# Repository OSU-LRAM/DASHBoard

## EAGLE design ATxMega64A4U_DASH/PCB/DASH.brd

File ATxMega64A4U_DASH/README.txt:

Bluetooth Device ID:
RNBT-990E

Authentification is:
1234

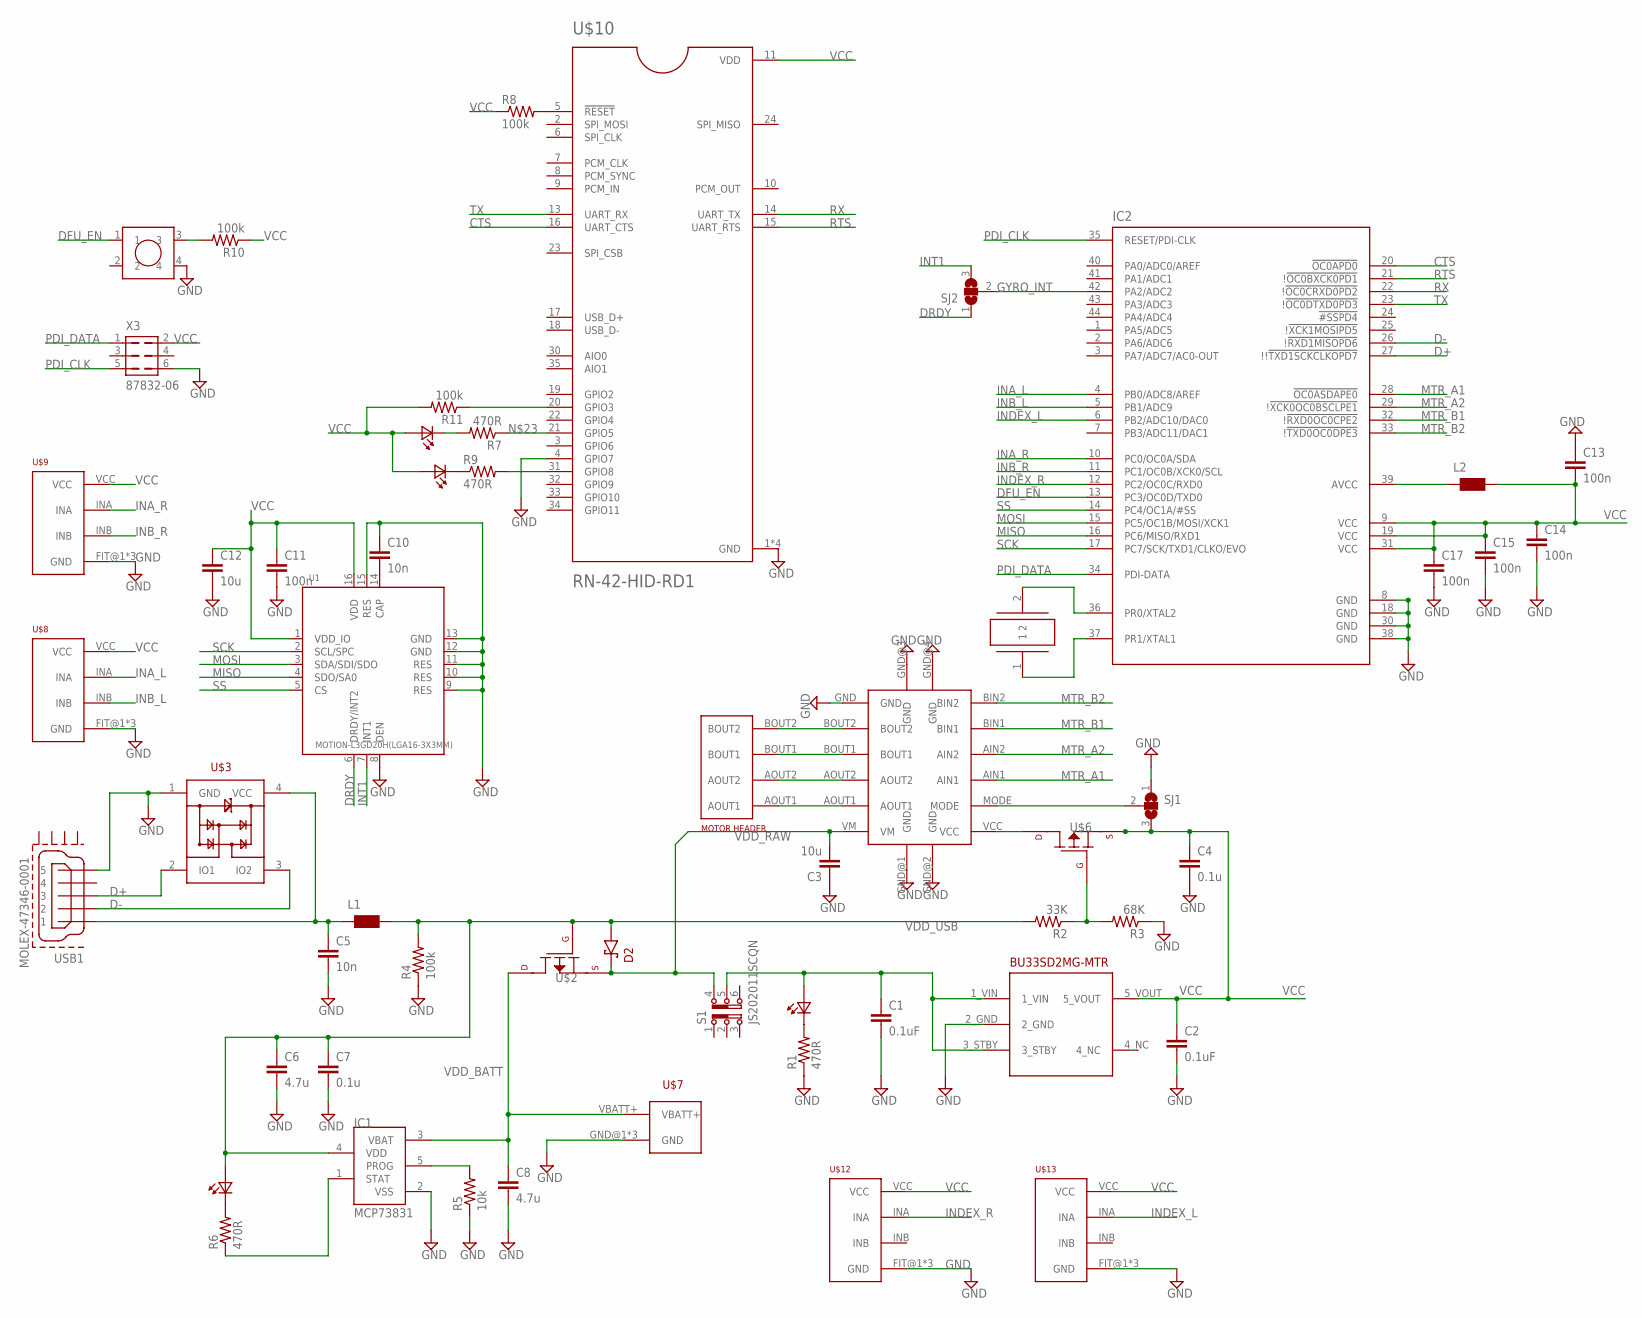
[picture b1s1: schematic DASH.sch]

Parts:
C1, C2: 0.1uF; 0603-CAP
C3, C12: 10u; C0805
C4, C7: 0.1u; C0603
C5, C10: 10n; C0603
C6, C8: 4.7u; C0603
C11, C13, C14, C15, C17: 100n; C0603
D1, D3, D5, D6: LTST-C190KRKT; 0603
D2: SCHOTTKY_DIODE_0805
IC1: MCP73831; SOT23-5L
IC2: AT-XMEGA-XXA4-AU; QFP80P1200X1200X120-44N
L1, L2: WE-CBF_0603; 0603
R1, R6, R7, R9: 470R; R0603
R2: 33K; R0603
R3: 68K; R0603
R4, R8, R10, R11: 100k; R0603
R5: 10k; R0603
S1: JS202011SCQN
SJ1, SJ2: SJ2W; SJ_2
U1: MOTION-L3GD20H(LGA16-3X3MM); LGA16-0.5-3X3MM
U$1: LDO_BU33SD2-MSURFACE_MOUNT; SSOP5
U$2, U$6: P-FETSMD; SOT-323
U$3: PRTR5V0U2X; SOT143B
U$4: DRV8835
U$5: SMB04-SRSS-TBSMD; SM04B-SRSS-TB
U$7: SM02B-SRSS
U$8, U$9, U$12, U$13: LEFT_ENCODER; SM04B-SRSS-TB
U$10: RN-42-HID-RD1; MICROCHIP_RN-42-HID-RD1
U$11: PUSHBUTTON
U$14: FC-12M_32.7
USB1: MOLEX-47346-0001; MOLEX-47364-0001
X3: 87832-06

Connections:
CTS: IC2.20 (!OC0APD0), U$10.16 (UART_CTS)
D+: IC2.27 (!!!TXD1SCKCLKOPD7), U$3.2 (IO1), USB1.3
D-: IC2.26 (!!RXD1MISOPD6), U$3.3 (IO2), USB1.2
DFU_EN: IC2.13 (PC3/OC0D/TXD0), U$11.1
DRDY: SJ2.1, U1.6 (DRDY/INT2)
GND: C1.2, C2.2, C3.1, C4.2, C5.2, C6.2, C7.2, C8.2, C10.1, C11.2, C12.2, C13.1, C14.2, C15.2, C17.2, IC1.2 (VSS), IC2.8 (GND), IC2.18 (GND), IC2.30 (GND), IC2.38 (GND), R1.1, R3.1, R4.1, R5.1, SJ1.1, U1.8 (DEN), U1.9 (RES), U1.10 (RES), U1.11 (RES), U1.12 (GND), U1.13 (GND), U1.15 (RES), U$1.2_GND, U$3.1 (GND), U$4.GND, U$4.GND@1 (GND), U$4.GND@2 (GND), U$4.GND@3 (GND), U$4.GND@4 (GND), U$4.GND@5 (GND), U$7.GND@1 (GND), U$7.GND@2 (GND), U$7.VBATT- (GND), U$8.FIT@1 (GND), U$8.FIT@2 (GND), U$8.GND, U$9.FIT@1 (GND), U$9.FIT@2 (GND), U$9.GND, U$10.1 (GND), U$10.4 (GPIO7), U$10.12 (GND), U$10.28 (GND), U$10.29 (GND), U$11.4, U$12.FIT@1 (GND), U$12.FIT@2 (GND), U$12.GND, U$13.FIT@1 (GND), U$13.FIT@2 (GND), U$13.GND, USB1.5, X3.6
GYRO_INT: IC2.42 (PA2/ADC2), SJ2.2
INA_L: IC2.4 (PB0/ADC8/AREF), U$8.INA
INA_R: IC2.10 (PC0/OC0A/SDA), U$9.INA
INB_L: IC2.5 (PB1/ADC9), U$8.INB
INB_R: IC2.11 (PC1/OC0B/XCK0/SCL), U$9.INB
INDEX_L: IC2.6 (PB2/ADC10/DAC0), U$13.INA
INDEX_R: IC2.12 (PC2/OC0C/RXD0), U$12.INA
INT1: SJ2.3, U1.7 (INT1)
MISO: IC2.16 (PC6/MISO/RXD1), U1.4 (SDO/SA0)
MOSI: IC2.15 (PC5/OC1B/MOSI/XCK1), U1.3 (SDA/SDI/SDO)
MTR_A1: IC2.28 (!OC0ASDAPE0), U$4.AIN1
MTR_A2: IC2.29 (!!XCK0OC0BSCLPE1), U$4.AIN2
MTR_B1: IC2.32 (!!RXD0OC0CPE2), U$4.BIN1
MTR_B2: IC2.33 (!!TXD0OC0DPE3), U$4.BIN2
unnamed: C1.1, D1.2 (A2), S1.5, U$1.1_VIN, U$1.3_STBY
unnamed: D1.1 (K2), R1.2
unnamed: R10.2, U$11.3
unnamed: U$4.AOUT1, U$5.AOUT1
unnamed: C10.2, U1.14 (CAP)
unnamed: U$4.AOUT2, U$5.AOUT2
unnamed: U$4.BOUT1, U$5.BOUT1
unnamed: U$4.BOUT2, U$5.BOUT2
unnamed: U$4.VCC, U$6.3_DRAIN
unnamed: R2.1, R3.2, U$6.1_GATE
unnamed: SJ1.2, U$4.MODE
unnamed: C5.1, L1.1, U$3.4 (VCC), USB1.1
unnamed: D3.1 (K2), R6.2
unnamed: IC1.5 (PROG), R5.2
unnamed: IC1.1 (STAT), R6.1
unnamed: D5.1 (K2), R7.2
unnamed: D6.1 (K2), R9.1
unnamed: IC2.36 (PR0/XTAL2), U$14.2
unnamed: IC2.37 (PR1/XTAL1), U$14.1
unnamed: IC2.39 (AVCC), L2.1
unnamed: R9.2, U$10.31 (GPIO8)
unnamed: R8.2, U$10.5 (!RESET)
unnamed: R7.1, U$10.21 (GPIO5)
unnamed: R11.1, U$10.20 (GPIO3)
PDI_CLK: IC2.35 (RESET/PDI-CLK), X3.5
PDI_DATA: IC2.34 (PDI-DATA), X3.1
RTS: IC2.21 (!!OC0BXCK0PD1), U$10.15 (UART_RTS)
RX: IC2.22 (!!OC0CRXD0PD2), U$10.14 (UART_TX)
SCK: IC2.17 (PC7/SCK/TXD1/CLKO/EVO), U1.2 (SCL/SPC)
SS: IC2.14 (PC4/OC1A/#SS), U1.5 (CS)
TX: IC2.23 (!!OC0DTXD0PD3), U$10.13 (UART_RX)
VCC: C2.1, C4.1, C11.1, C12.1, C13.2, C14.1, C15.1, C17.1, D5.2 (A2), D6.2 (A2), IC2.9 (VCC), IC2.19 (VCC), IC2.31 (VCC), L2.2, R8.1, R10.1, R11.2, SJ1.3, U1.1 (VDD_IO), U1.16 (VDD), U$1.5_VOUT, U$6.2_SOURCE, U$8.VCC, U$9.VCC, U$10.11 (VDD), U$12.VCC, U$13.VCC, X3.2
VDD_BATT: C8.1, IC1.3 (VBAT), U$2.3_DRAIN, U$7.VBATT+
VDD_RAW: C3.2, D2.1_CATHODE, S1.4, U$2.2_SOURCE, U$4.VM
VDD_USB: C6.1, C7.1, D2.2_ANODE, D3.2 (A2), IC1.4 (VDD), L1.2, R2.2, R4.2, U$2.1_GATE

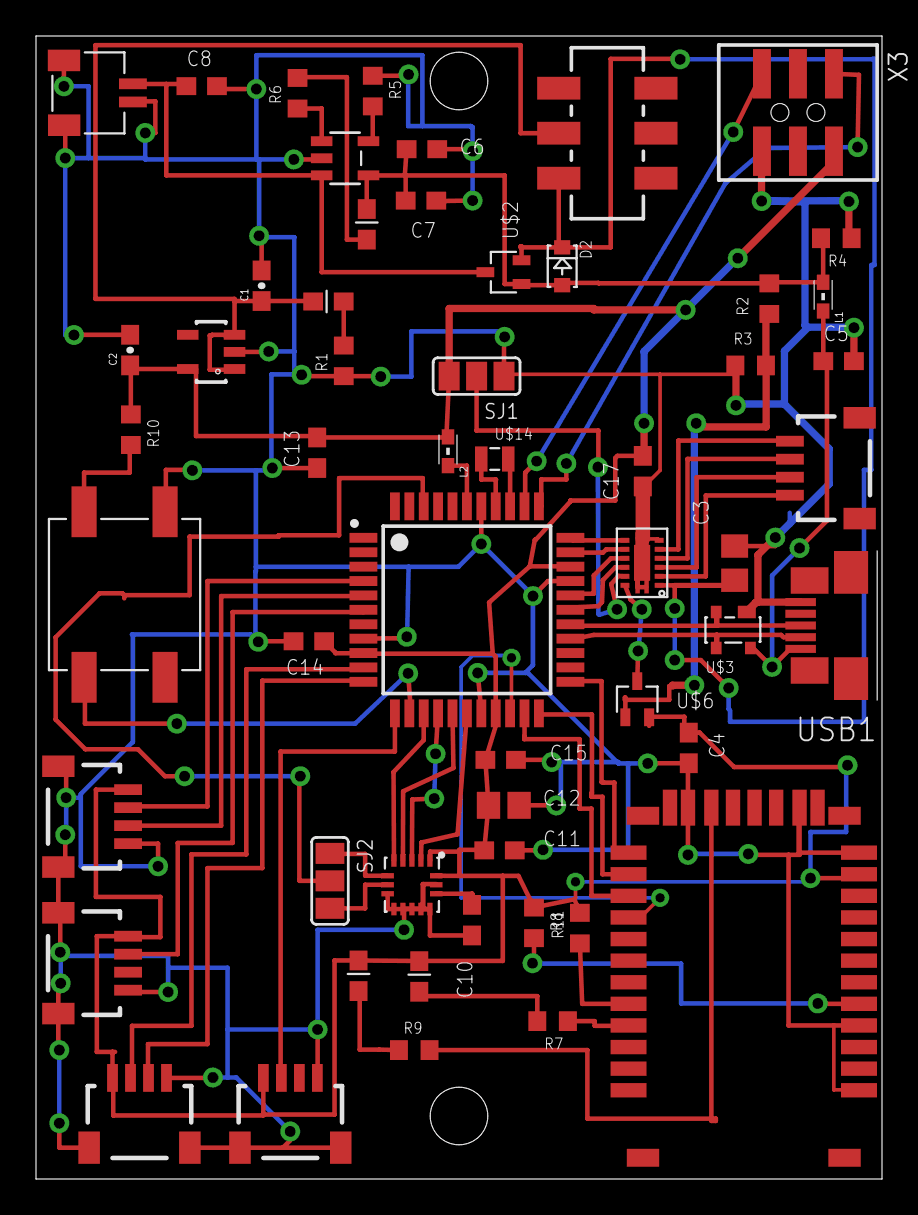
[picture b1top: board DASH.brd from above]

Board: 2 copper layers, 47.0 x 63.5 mm, 55 parts (0 on the bottom side), 55 nets.

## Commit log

2016-06-20 First massive commit of DASH board. Both code for the Dash Board itself and the GUI.
2016-06-24 Added Readme to the ATxMEGA..._DASH described a little bit about the Bluetooth
2016-06-24 Added .gitingnore file for compiled and object files.

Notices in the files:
parts and their libraries:
switch-ck: Copyright (C) 2011, Bob Starr
SparkFun-Capacitors: Licensing: Creative Commons ShareAlike 4.0 International - https://creativecommons.org/licenses/by-sa/4.0
wuerth-elektronik: Copyright: Würth Elektronik eiSos
